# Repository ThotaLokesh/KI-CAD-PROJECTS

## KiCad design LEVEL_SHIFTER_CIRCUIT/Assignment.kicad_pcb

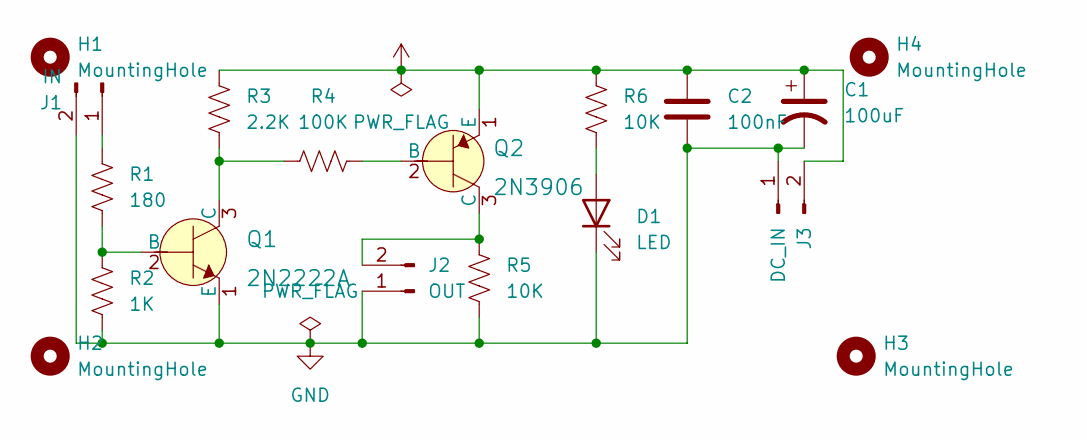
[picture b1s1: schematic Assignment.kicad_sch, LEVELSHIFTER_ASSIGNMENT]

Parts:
C1: 100uF; C_Rect_L7.0mm_W2.5mm_P5.00mm
C2: 100nF; C_Rect_L7.0mm_W2.5mm_P5.00mm
D1: LED; LED_D3.0mm
H1, H2, H3, H4: MountingHole; MountingHole_3.2mm_M3
J1: IN; Molex_KK-254_AE-6410-02A_1x02_P2.54mm_Vertical
J2: OUT; Molex_KK-254_AE-6410-02A_1x02_P2.54mm_Vertical
J3: DC_IN; Molex_KK-396_A-41791-0002_1x02_P3.96mm_Vertical
Q1: 2N2222A; MPN 2N2222A; Digi-Key_PN 2N2222ACS-ND
Q2: 2N3906; TO-92-3; MPN 2N3906; Digi-Key_PN 2N3906CS-ND
R1: 180; R_Axial_DIN0207_L6.3mm_D2.5mm_P7.62mm_Horizontal
R2: 1K; R_Axial_DIN0207_L6.3mm_D2.5mm_P7.62mm_Horizontal
R3: 2.2K; R_Axial_DIN0207_L6.3mm_D2.5mm_P7.62mm_Horizontal
R4: 100K; R_Axial_DIN0207_L6.3mm_D2.5mm_P7.62mm_Horizontal
R5, R6: 10K; R_Axial_DIN0207_L6.3mm_D2.5mm_P7.62mm_Horizontal

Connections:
+12V: C1.1, C2.1, J3.2, Q2.1 (E), R3.1, R6.1
GND: C1.2, C2.2, D1.1 (K), J1.2, J2.1, J3.1, Q1.1 (E), R2.2, R5.2
unnamed: D1.2 (A), R6.2
unnamed: J1.1, R1.2
unnamed: J2.2, Q2.3 (C), R5.1
unnamed: Q1.2 (B), R1.1, R2.1
unnamed: Q1.3 (C), R3.2, R4.1
unnamed: Q2.2 (B), R4.2

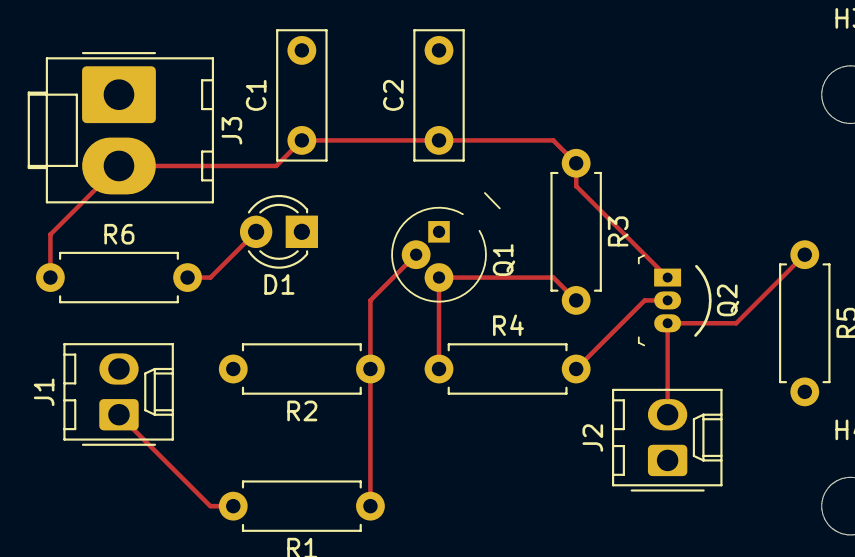
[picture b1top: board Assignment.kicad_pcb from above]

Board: 2 copper layers, 18 parts (0 on the bottom side), 8 nets.

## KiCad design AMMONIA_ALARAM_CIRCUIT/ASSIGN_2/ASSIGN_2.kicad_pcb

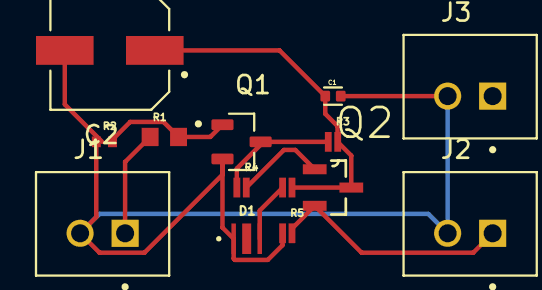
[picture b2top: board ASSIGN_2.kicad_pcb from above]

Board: 2 copper layers, 14 parts (0 on the bottom side), 8 nets.

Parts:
C1: CL05A104KA5NNNC; CAPC1005X55N
C2: EEEHAE101XAP; CAP_EEEHAE101XAP
D1: L1SP-DRD0002000000; LED_L1SP-DRD0002000000
J1, J2, J3: B2B-XH-A(LF)(SN); JST_B2B-XH-A(LF)(SN)
Q1: MMBT2222ALT1; SOT95P237X111-3N
Q2: MMBT3906-7-F; SOT103P240X110-3N
R1: RG1608P-181-B-T5; RESC1608X50N
R2: ESR01MZPJ102; RESC1005X40N
R3: WK73R1ETTP222J; RESC0510X40N
R4: WK73R1ETTP104J; RESC0510X40N
R5, R6: WK73R1ETTP103J; RESC0510X40N

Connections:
GND: C1.2, C2.2, D1.K, J1.2, J2.2, J3.2, Q1.2, R2.1, R5.1
unnamed: C1.1, C2.1, Q2.3 (E), R3.2, R6.2
unnamed: D1.A, R6.1
unnamed: J2.1, Q2.2 (C), R5.2
unnamed: Q1.1, R1.2, R2.2
unnamed: Q1.3, R3.1, R4.1
unnamed: Q2.1 (B), R4.2
unnamed: J1.1, R1.1

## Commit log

2022-08-26 MINI PROJECTS OF PCB DESIGNING
